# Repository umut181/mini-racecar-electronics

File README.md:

# Mini Racecar Electronics

A custom electronics board for a **2WD, IR-controlled differential-drive robot vehicle**, designed in **KiCad**.

---

## Overview

| | |
|---|---|
| **Form factor** | < 100 mm × 100 mm |
| **Fabrication** | 2-layer rigid FR-4, via Robotistan PCB Service |
| **Battery input** | 2S–6S LiPo (4.5 V – 40 V input range) |
| **Logic compatibility** | Any 5 V-based microcontroller |
| **Motor support** | Low-reduction 3–6 V TT motors, 150 mA (no load) – 1.5 A (stall) |

---

## Power & Drive Architecture

The board combines a **buck-style power stage** (inductor + Schottky + electrolytic caps) to step the LiPo input down for logic rails, and a **dual full H-bridge** built from discrete `IRF540N` MOSFETs (driven via `IR2104` half-bridge drivers) to independently control two DC motors for differential steering. IR receiver pins bring in the remote-control signal.

---

## Bill of Materials

### Power Stage

| Ref | Value | Notes |
|---|---|---|
| L1 | 33 µH | Radial inductor, Fastron 07HCP |
| D1 | 5 A / 100 V Schottky | Buck rectifier |
| Q — power switching | 8× IRF540N | TO-220, vertical |
| IC — gate drivers | 4× IR2104 | DIP-8, half-bridge driver |

### Capacitors

| Ref | Value | Package |
|---|---|---|
| C1 | 100 µF / 16 V | Electrolytic |
| C2 | 220 µF / 16 V | Electrolytic |
| C9 | 470 µF / 16 V | Electrolytic |
| C12 | 470 µF / 16 V | Electrolytic |
| C7, C13 | 1 µF | SMD 1206 |
| C8, C15 | 10 µF | SMD 1206 |
| C3, C4, C11, C14 | 0.47 µF | SMD 0805 |
| C5, C6, C10, C16 | 0.1 µF | SMD 0805 |

### Diodes

| Ref | Value | Package |
|---|---|---|
| D1 | 5 A / 100 V Schottky | — |
| D2, D3, D4, D5, D6, D10, D11, D12 | 1N4148 | THT DO-35, 7.62 mm |
| D7, D8, D9, D13 | MURS260 | SMD, SMB |

### MOSFETs & Gate Drive

| Ref | Part | Package |
|---|---|---|
| Q1–Q8 | IRF540N | TO-220-3, vertical |
| IR2104 ×4 | Half-bridge driver | DIP-8 |

### Resistors

| Ref | Value (Ω) | Package |
|---|---|---|
| R1, R2, R3, R4, R6, R7, R9, R10 | 10 | SMD 0805 |
| R5, R8 | 0.1 (current sense) | SMD 0805 |

### Connectors

| Ref | Type | Footprint |
|---|---|---|
| Load1, Load2, Input | 2-pin terminal block | MaiXu MX126-5.0-02P, 5.00 mm pitch |
| IR_pins | 3-pin header | 2.54 mm pin header, vertical |
| IR_pins1 | Custom | — |

---

## Tooling

Designed entirely in **KiCad**.

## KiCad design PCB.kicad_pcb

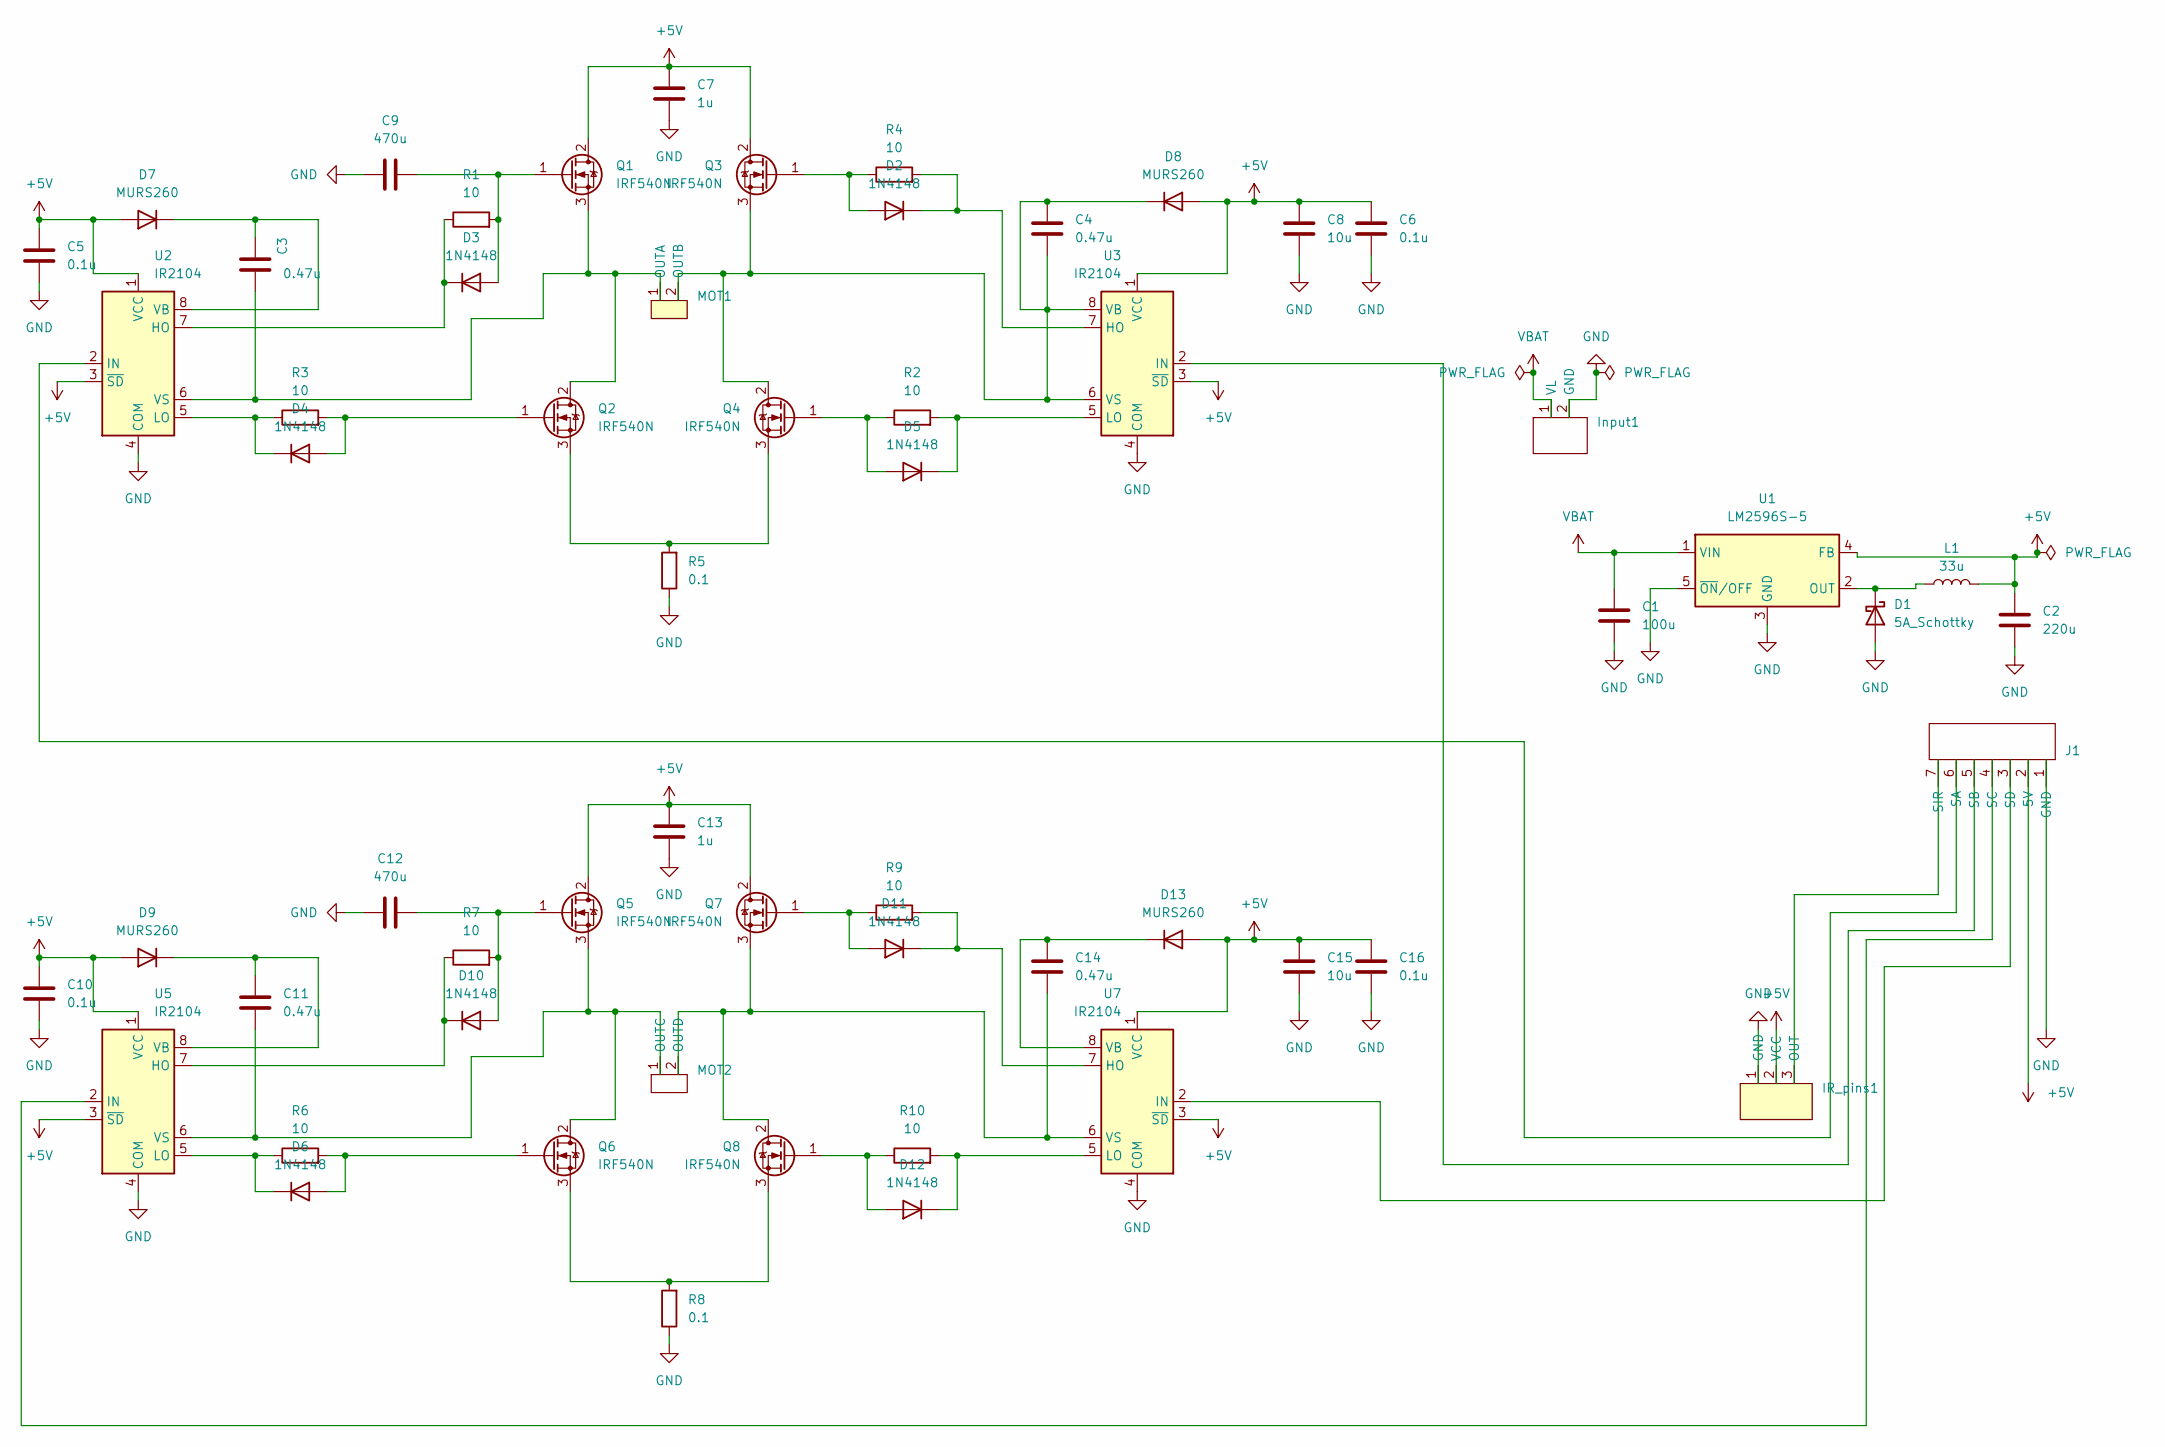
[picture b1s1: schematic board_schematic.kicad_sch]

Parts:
C1: 100u; CP_Axial_L11.0mm_D5.0mm_P18.00mm_Horizontal
C2: 220u; CP_Axial_L11.0mm_D6.0mm_P18.00mm_Horizontal
C3, C4, C11, C14: 0.47u; C_0805_2012Metric_Pad1.18x1.45mm_HandSolder
C5, C6, C10, C16: 0.1u; C_0805_2012Metric_Pad1.18x1.45mm_HandSolder
C7, C13: 1u; C_1206_3216Metric_Pad1.33x1.80mm_HandSolder
C8, C15: 10u; C_1206_3216Metric_Pad1.33x1.80mm_HandSolder
C9, C12: 470u; C_Axial_L12.0mm_D8.5mm_P15.00mm_Horizontal
D1: 5A_Schottky; D_DO-201AD_P5.08mm_Vertical_AnodeUp
D2, D3, D4, D5, D6, D10, D11, D12: 1N4148; D_DO-35_SOD27_P7.62mm_Horizontal
D7, D8, D9, D13: MURS260; D_SMB_Handsoldering
IR_pins1: PinSocket_1x03_P2.54mm_Vertical
Input1: TerminalBlock_MaiXu_MX126-5.0-02P_1x02_P5.00mm
J1: PinHeader_1x07_P2.54mm_Vertical
L1: 33u; L_Radial_D7.8mm_P5.00mm_Fastron_07HCP
MOT1, MOT2: TerminalBlock_MaiXu_MX126-5.0-02P_1x02_P5.00mm
Q1, Q2, Q3, Q4, Q5, Q6, Q7, Q8: IRF540N; TO-220-3_Vertical
R1, R2, R3, R4, R6, R7, R9, R10: 10; R_0805_2012Metric_Pad1.20x1.40mm_HandSolder
R5, R8: 0.1; R_0805_2012Metric_Pad1.20x1.40mm_HandSolder
U1: LM2596S-5; TO-263-5_TabPin3
U2, U3, U5, U7: IR2104; DIP-8_W7.62mm

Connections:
+5V: C2.1, C5.1, C6.1, C7.1, C8.1, C10.1, C13.1, C15.1, C16.1, D7.2 (A), D8.2 (A), D9.2 (A), D13.2 (A), IR_pins1.2 (VCC), J1.2 (5V), L1.2, Q1.2 (D), Q3.2 (D), Q5.2 (D), Q7.2 (D), U1.4 (FB), U2.1 (VCC), U2.3 (~SD), U3.1 (VCC), U3.3 (~SD), U5.1 (VCC), U5.3 (~SD), U7.1 (VCC), U7.3 (~SD)
GND: C1.2, C2.2, C5.2, C6.2, C7.2, C8.2, C9.1, C10.2, C12.1, C13.2, C15.2, C16.2, D1.2 (A), IR_pins1.1 (GND), Input1.2 (GND), J1.1 (GND), R5.1, R8.1, U1.3 (GND), U1.5 (~ON/OFF), U2.4 (COM), U3.4 (COM), U5.4 (COM), U7.4 (COM)
unnamed: D1.1 (K), L1.1, U1.2 (OUT)
unnamed: D2.2 (A), Q3.1 (G), R4.1
unnamed: D2.1 (K), R4.2, U3.7 (HO)
unnamed: C9.2, D3.2 (A), Q1.1 (G), R1.2
unnamed: D3.1 (K), R1.1, U2.7 (HO)
unnamed: D4.2 (A), Q2.1 (G), R3.2
unnamed: D4.1 (K), R3.1, U2.5 (LO)
unnamed: D5.2 (A), Q4.1 (G), R2.1
unnamed: D5.1 (K), R2.2, U3.5 (LO)
unnamed: D6.2 (A), Q6.1 (G), R6.2
unnamed: D6.1 (K), R6.1, U5.5 (LO)
unnamed: C3.1, D7.1 (K), U2.8 (VB)
unnamed: C4.1, C4.2, D8.1 (K), MOT1.2 (OUTB), Q3.3 (S), Q4.2 (D), U3.6 (VS), U3.8 (VB)
unnamed: C11.1, D9.1 (K), U5.8 (VB)
unnamed: C12.2, D10.2 (A), Q5.1 (G), R7.2
unnamed: D10.1 (K), R7.1, U5.7 (HO)
unnamed: D11.2 (A), Q7.1 (G), R9.1
unnamed: D11.1 (K), R9.2, U7.7 (HO)
unnamed: D12.2 (A), Q8.1 (G), R10.1
unnamed: D12.1 (K), R10.2, U7.5 (LO)
unnamed: C14.1, D13.1 (K), U7.8 (VB)
unnamed: IR_pins1.3 (OUT), J1.7 (SIR)
unnamed: J1.6 (SA), U2.2 (IN)
unnamed: J1.5 (SB), U3.2 (IN)
unnamed: J1.4 (SC), U5.2 (IN)
unnamed: J1.3 (SD), U7.2 (IN)
unnamed: C3.2, MOT1.1 (OUTA), Q1.3 (S), Q2.2 (D), U2.6 (VS)
unnamed: C11.2, MOT2.1 (OUTC), Q5.3 (S), Q6.2 (D), U5.6 (VS)
unnamed: C14.2, MOT2.2 (OUTD), Q7.3 (S), Q8.2 (D), U7.6 (VS)
unnamed: Q2.3 (S), Q4.3 (S), R5.2
unnamed: Q6.3 (S), Q8.3 (S), R8.2
VBAT: C1.1, Input1.1 (VL), U1.1 (VIN)

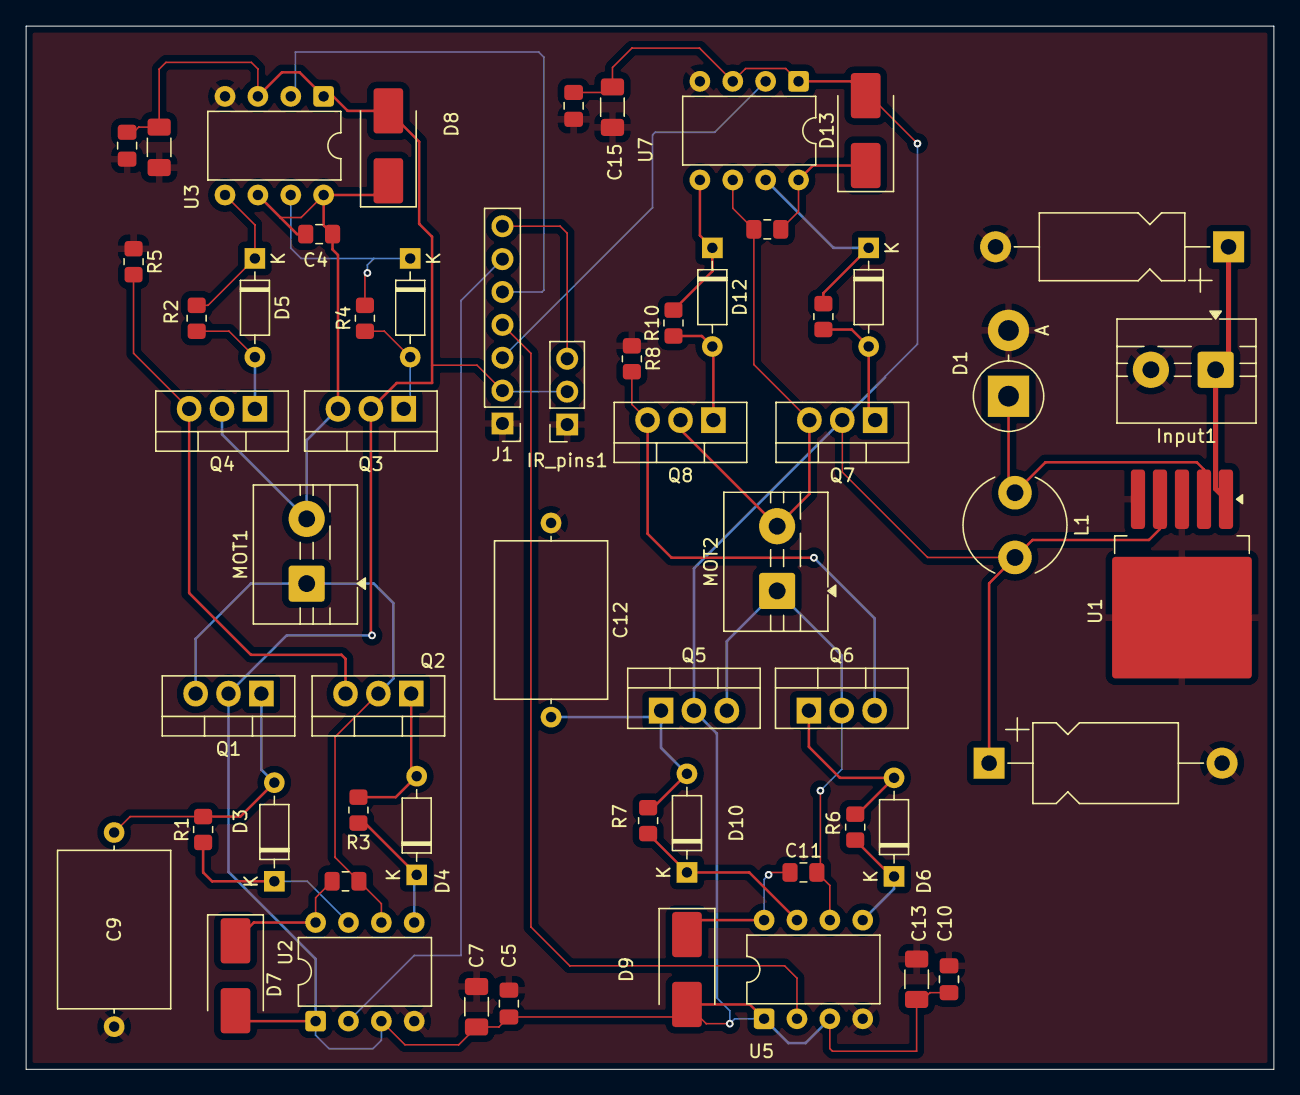
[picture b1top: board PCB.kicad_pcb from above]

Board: 4 copper layers, 96.4 x 80.6 mm, 58 parts (0 on the bottom side), 34 nets.
